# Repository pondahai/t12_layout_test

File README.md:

# t12_layout_test

TBD  

reference:

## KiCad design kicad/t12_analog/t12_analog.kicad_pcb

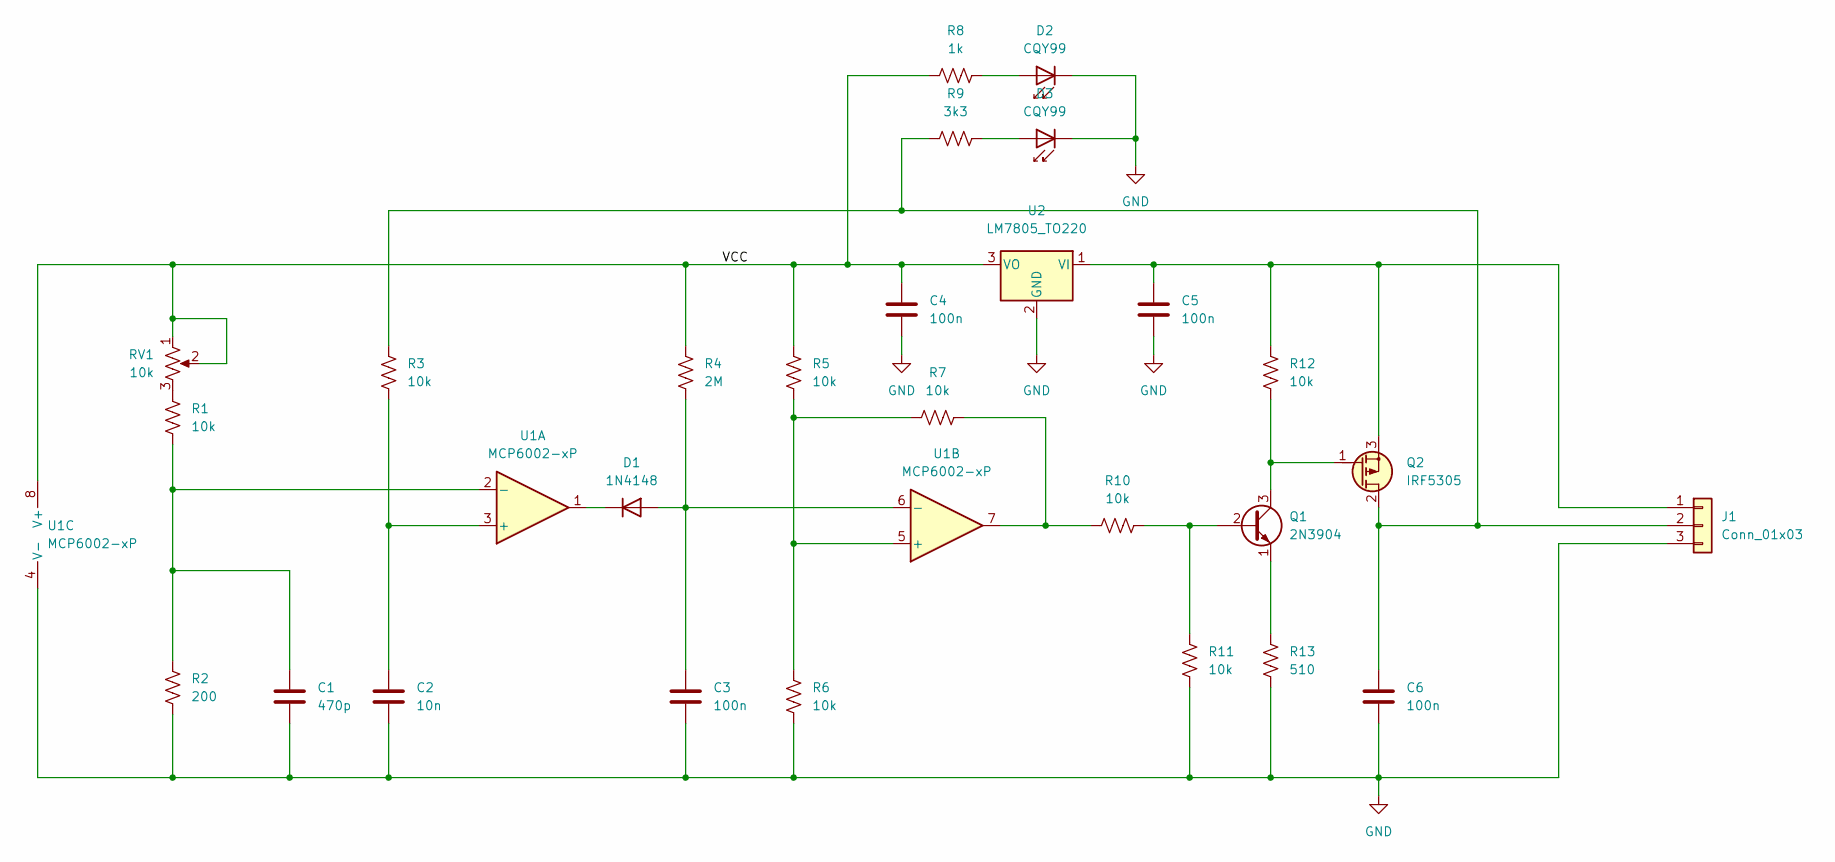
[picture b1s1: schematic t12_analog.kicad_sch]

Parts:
C1: 470p; C_Disc_D5.0mm_W2.5mm_P5.00mm
C2: 10n; C_Disc_D5.0mm_W2.5mm_P5.00mm
C3, C4, C5, C6: 100n; C_Disc_D5.0mm_W2.5mm_P5.00mm
D1: 1N4148; D_DO-35_SOD27_P7.62mm_Horizontal
D2, D3: CQY99; LED_D5.0mm_IRGrey
J1: Conn_01x03; PinHeader_1x03_P2.54mm_Vertical
Q1: 2N3904; TO-92_Inline
Q2: IRF5305; TO-220-3_Vertical
R1, R3, R5, R6, R7, R10, R11, R12: 10k; R_Axial_DIN0207_L6.3mm_D2.5mm_P10.16mm_Horizontal
R2: 200; R_Axial_DIN0207_L6.3mm_D2.5mm_P10.16mm_Horizontal
R4: 2M; R_Axial_DIN0207_L6.3mm_D2.5mm_P10.16mm_Horizontal
R8: 1k; R_Axial_DIN0207_L6.3mm_D2.5mm_P10.16mm_Horizontal
R9: 3k3; R_Axial_DIN0207_L6.3mm_D2.5mm_P10.16mm_Horizontal
R13: 510; R_Axial_DIN0207_L6.3mm_D2.5mm_P10.16mm_Horizontal
RV1: 10k; Potentiometer_Alps_RK163_Single_Horizontal
U1: MCP6002-xP; DIP-8_W7.62mm_Socket_LongPads
U2: LM7805_TO220; TO-220-3_Vertical

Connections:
/VCC: C4.1, R4.1, R5.1, R8.1, RV1.1, RV1.2, U1.8 (V+), U2.3 (VO)
GND: C1.2, C2.2, C3.2, C4.2, C5.2, C6.2, D2.1 (K), D3.1 (K), J1.3, R2.2, R6.2, R11.1, R13.1, U1.4 (V-), U2.2 (GND)
unnamed: C1.1, R1.2, R2.1, U1.2 (-)
unnamed: C2.1, R3.2, U1.3 (+)
unnamed: C3.1, D1.2 (A), R4.2, U1.6 (-)
unnamed: C5.1, J1.1, Q2.3 (S), R12.2, U2.1 (VI)
unnamed: C6.1, J1.2, Q2.2 (D), R3.1, R9.1
unnamed: D1.1 (K), U1.1
unnamed: D2.2 (A), R8.2
unnamed: D3.2 (A), R9.2
unnamed: Q1.1 (E), R13.2
unnamed: Q1.2 (B), R10.2, R11.2
unnamed: Q1.3 (C), Q2.1 (G), R12.1
unnamed: R1.1, RV1.3
unnamed: R5.2, R6.1, R7.1, U1.5 (+)
unnamed: R7.2, R10.1, U1.7

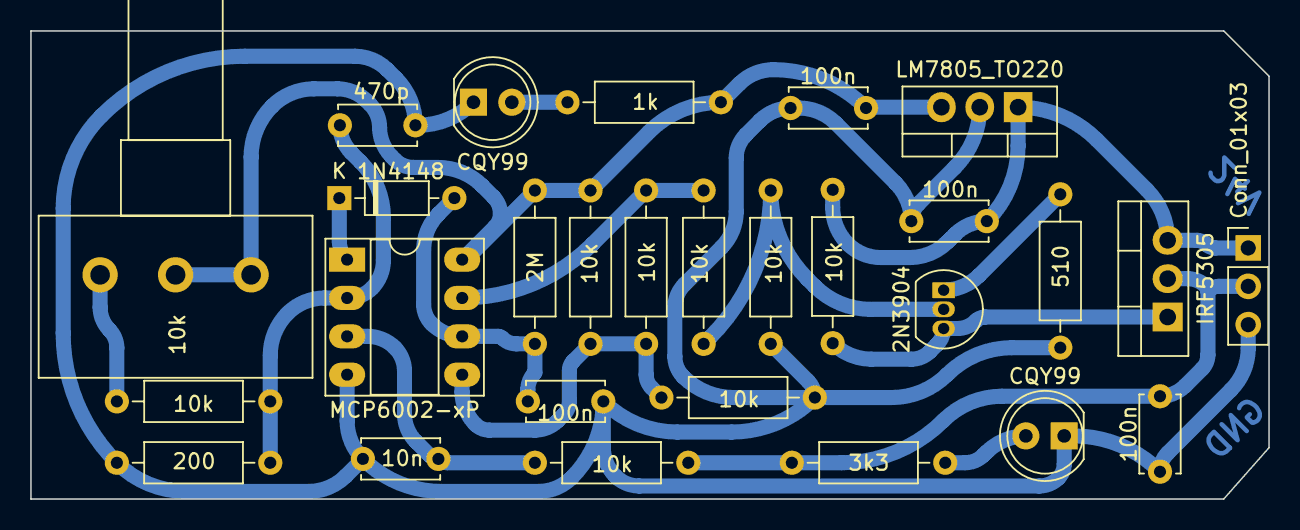
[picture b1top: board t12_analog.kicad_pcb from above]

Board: 2 copper layers, 82.0 x 31.0 mm, 28 parts (0 on the bottom side), 16 nets.
